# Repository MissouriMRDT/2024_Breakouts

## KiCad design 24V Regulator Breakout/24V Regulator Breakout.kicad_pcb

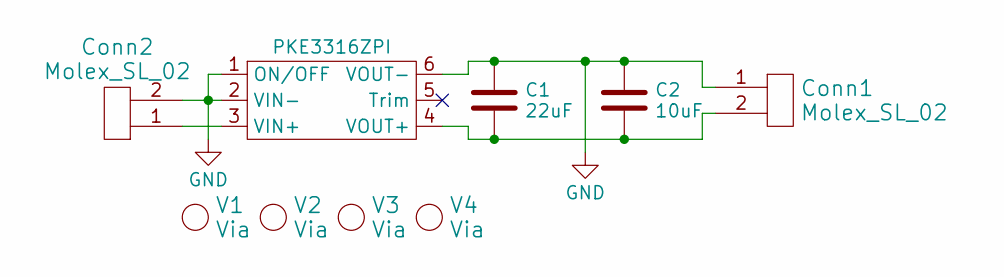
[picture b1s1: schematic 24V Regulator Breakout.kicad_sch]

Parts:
C1: 22uF; CP_Radial_D5.0mm_P2.00mm
C2: 10uF; C_1206_3216Metric_Pad1.33x1.80mm_HandSolder
Conn1, Conn2: Molex_SL_02; MOLEX_SL_02_Horizontal
U1: PKE3316ZPI
V1, V2, V3, V4: Via; 4_40_Hole

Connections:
GND: C1.1, C2.1, Conn1.1, Conn2.2, U1.1 (ON/OFF), U1.2 (VIN-), U1.6 (VOUT-)
unnamed: Conn2.1, U1.3 (VIN+)
unnamed: C1.2, C2.2, Conn1.2, U1.4 (VOUT+)

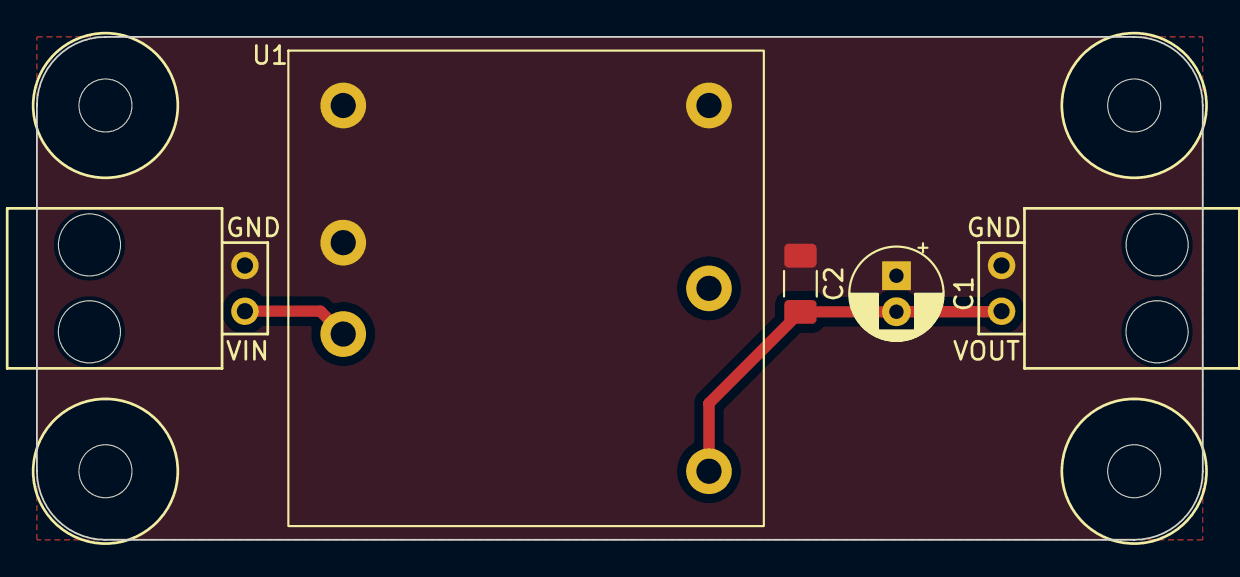
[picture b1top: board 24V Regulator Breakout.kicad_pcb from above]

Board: 2 copper layers, 64.8 x 27.9 mm, 9 parts (0 on the bottom side), 3 nets.

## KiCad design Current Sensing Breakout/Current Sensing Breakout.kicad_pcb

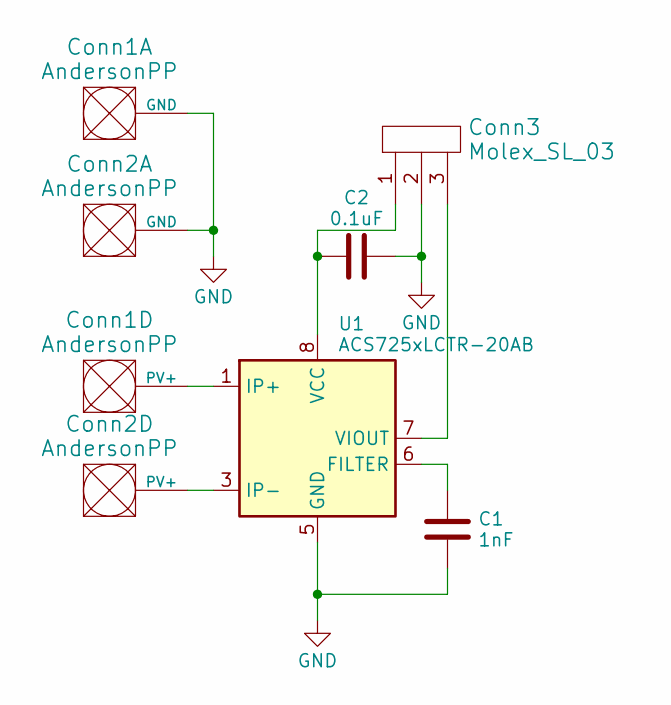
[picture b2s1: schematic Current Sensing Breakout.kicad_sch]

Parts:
C1: 1nF; C_0603_1608Metric_Pad1.08x0.95mm_HandSolder
C2: 0.1uF; C_0603_1608Metric_Pad1.08x0.95mm_HandSolder
Conn1, Conn2: AndersonPP; Square_Anderson_2_H_Side_By_Side_PV
Conn3: Molex_SL_03; MOLEX_SL_03_Horizontal
U1: ACS725xLCTR-20AB; SOIC-8_3.9x4.9mm_P1.27mm

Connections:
GND: C1.2, C2.2, Conn1.1 (GND), Conn2.1 (GND), Conn3.2, U1.5 (GND)
unnamed: Conn1.4 (PV+), U1.1 (IP+), U1.2 (IP+)
unnamed: Conn2.4 (PV+), U1.3 (IP-), U1.4 (IP-)
unnamed: C1.1, U1.6 (FILTER)
unnamed: C2.1, Conn3.1, U1.8 (VCC)
unnamed: Conn3.3, U1.7 (VIOUT)

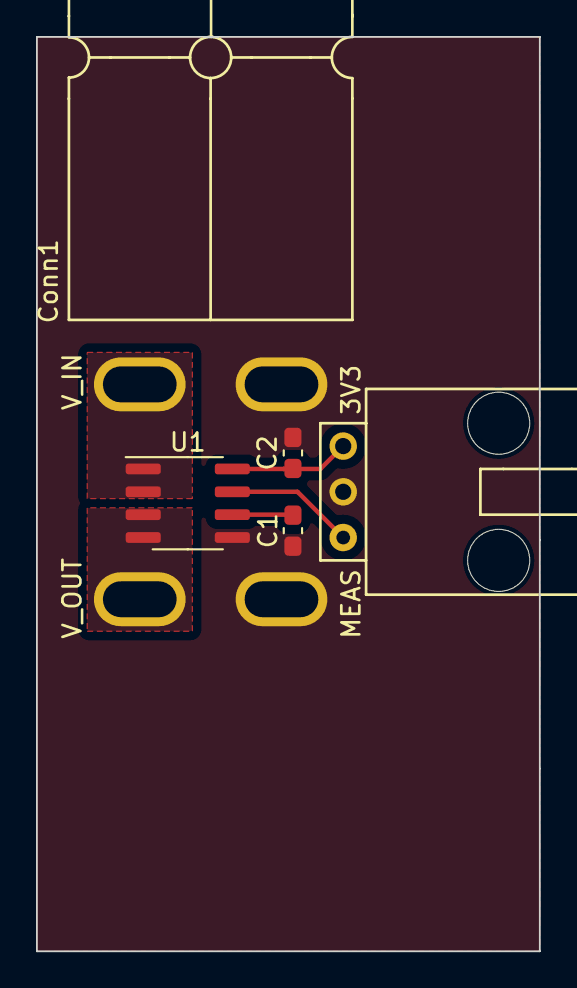
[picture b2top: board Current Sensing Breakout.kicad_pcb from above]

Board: 2 copper layers, 27.9 x 50.8 mm, 6 parts (1 on the bottom side), 6 nets.

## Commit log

2023-09-18 Current Sensing Breakout Created
2023-09-24 Added silkscreen to board
2023-09-24 Reorganized schematic
2023-09-24 Created 24V breakout schematic
2023-09-28 Finished Breakout Layout
2023-09-28 Fixed Capacitance Value
2023-09-28 Added Silkscreen
2023-09-29 Fixed Silkscreen
2023-10-05 Fixed Capacitor
2023-10-05 Generated Gerbs
2023-11-03 Created step file
